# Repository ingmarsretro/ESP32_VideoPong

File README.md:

# ESP32 PAL Pong - Vectorgameboard V1.0

Dieses Projekt ist eine klassische Pong-Umsetzung für den **ESP32**, die ein echtes **PAL-Videosignal** (Composite/FBAS) direkt über einen GPIO erzeugt. Ursprünglich als Demonstration für einen FH-Tag entwickelt, nutzt der Code das volle Potenzial des eigens dafür entwickelten **Vectorgameboards**.

## 🚀 Das Vectorgameboard V1.0
Passend zu dieser Software wurde eine dedizierte Platine entwickelt, die den ESP32 aufnimmt und alle notwendigen Komponenten "on-board" vereint:

*   **All-in-One Design:** Integrierte Potentiometer, Taster sowie Buchsen für Video- und Audio-Out.
*   **Audio-System:** Ein kleiner Lautsprecher samt Verstärker ist direkt auf dem Board verbaut.
*   **Dual-Mode Hardware:** Das Board ist sowohl für Composite-Video (PAL/NTSC) als auch für **ESP Vector Software** (X-Y-Modus für Oszilloskope) ausgelegt.
*   **Externer DAC:** Für die hochpräzise Vektordarstellung ist ein externer DAC verbaut.
*   **Open Hardware:** Details zu den Verbindungen, der Bestückung und dem Design finden sich in den **Schaltplänen** und **Eagle-Layouts** in diesem Repository.

## 📺 Software-Features
*   **PAL-Ausgabe:** Erzeugung eines Composite-Signals auf **PIN 25**.
*   **Spielmodi:** Wahl zwischen Singleplayer (gegen KI) und lokalem Multiplayer (1vs1).
*   **Steuerung:** Analoges Paddle-Feeling durch die Nutzung der On-Board Potentiometer.
*   **Grafik:** Integration von Bitmaps (Avatar/Logo) und Text via Bitluni-Library.
*   **Sound:** Akustisches Feedback bei Ballkontakt, Punktgewinn und Spielende.

## ⚠️ Wichtige Kompilier-Hinweise
Da die Video-Generierung extrem zeitkritisch ist, müssen zwingend folgende Library-Versionen verwendet werden. **Versionen der 3.x.x Schiene sind aktuell nicht kompatibel!**

| Komponente | Version |
| :--- | :--- |
| **ESP32 by Espressif Systems** | `2.0.0` |
| **Arduino ESP32 Boards** | `2.0.11` |
| **bitluni ESP32Lib** | `0.3.1` |

*Hinweis: Beim Kompilieren auftretende Warnungen können ignoriert werden.*

## 🛠 Hardware-Belegung (Pinout)
| Komponente | GPIO | Beschreibung |
| :--- | :--- | :--- |
| **Video Out** | 25 | Composite Signal |
| **Buzzer/Audio** | 27 | Soundausgabe (interner Verstärker) |
| **Poti 1** | 35 | Player 1 (Links) |
| **Poti 2** | 34 | Player 2 (Rechts) |
| **Button 1** | 32 | Modus wechseln |
| **Button 2** | 33 | Start / Aktion |

## 📜 Credits
*   **Hardware & Software:** ingmarsretro (Stand: Feb. 2026)
*   **Video Library:** Ein Dank geht an [bitluni](https://github.com) für die Bereitstellung der `ESP32Lib`.

---
*Viel Spaß beim Retrogaming auf dem Oszilloskop oder Röhrenfernseher!*

# ESP32 PAL Pong - Vectorgameboard V1.0

This project is a classic Pong implementation for the **ESP32**, generating a real **PAL composite video signal** (FBAS) directly via GPIO. originally developed as a demonstration for a university tech-day, this code utilizes the full potential of the custom-designed **Vectorgameboard**.

## 🚀 The Vectorgameboard V1.0
To support this software, a dedicated PCB was developed that houses the ESP32 and integrates all necessary components on-board:

*   **All-in-One Design:** Includes on-board potentiometers, buttons, and dedicated jacks for Video and Audio Out.
*   **Audio System:** Features a built-in small speaker and an integrated amplifier for immediate sound feedback.
*   **Dual-Mode Hardware:** The board is designed for both Composite Video (PAL/NTSC) and **ESP Vector Software** (X-Y mode for oscilloscopes).
*   **External DAC:** A dedicated external DAC is included for high-precision vector rendering on analog screens.
*   **Open Hardware:** Detailed schematics and **Eagle layouts** are available within this repository.

## 📺 Software Features
*   **PAL Output:** Generates a composite signal on **PIN 25**.
*   **Game Modes:** Toggle between Singleplayer (vs. AI) and local Multiplayer (1vs1).
*   **Precision Control:** Authentic analog paddle feeling using the on-board potentiometers.
*   **Graphics:** Integration of custom bitmaps (avatar/logo) and text overlays via the Bitluni library.
*   **Sound:** Haptic audio feedback for ball collisions, scoring, and game-over states.

## ⚠️ Critical Compilation Notes
Video generation on the ESP32 is extremely time-sensitive. To compile successfully, you **must** use the following library versions. **Versions 3.x.x are currently not compatible!**

| Component | Version |
| :--- | :--- |
| **ESP32 by Espressif Systems** | `2.0.0` |
| **Arduino ESP32 Boards** | `2.0.11` |
| **bitluni ESP32Lib** | `0.3.1` |

*Note: You can safely ignore compiler warnings during the build process.*

## 🛠 Hardware Pinout
| Component | GPIO | Description |
| :--- | :--- | :--- |
| **Video Out** | 25 | Composite Signal |
| **Buzzer/Audio** | 27 | Audio Output (Internal Amp) |
| **Pot 1** | 35 | Player 1 (Left) |
| **Pot 2** | 34 | Player 2 (Right) |
| **Button 1** | 32 | Change Mode |
| **Button 2** | 33 | Start / Action |

## 📜 Credits
*   **Hardware & Software:** ingmarsretro (Released: Feb. 2026)
*   **Video Library:** Special thanks to [bitluni](https://github.com) for the excellent `ESP32Lib`.

---
*Have fun retrogaming on your CRT TV or Oscilloscope!*

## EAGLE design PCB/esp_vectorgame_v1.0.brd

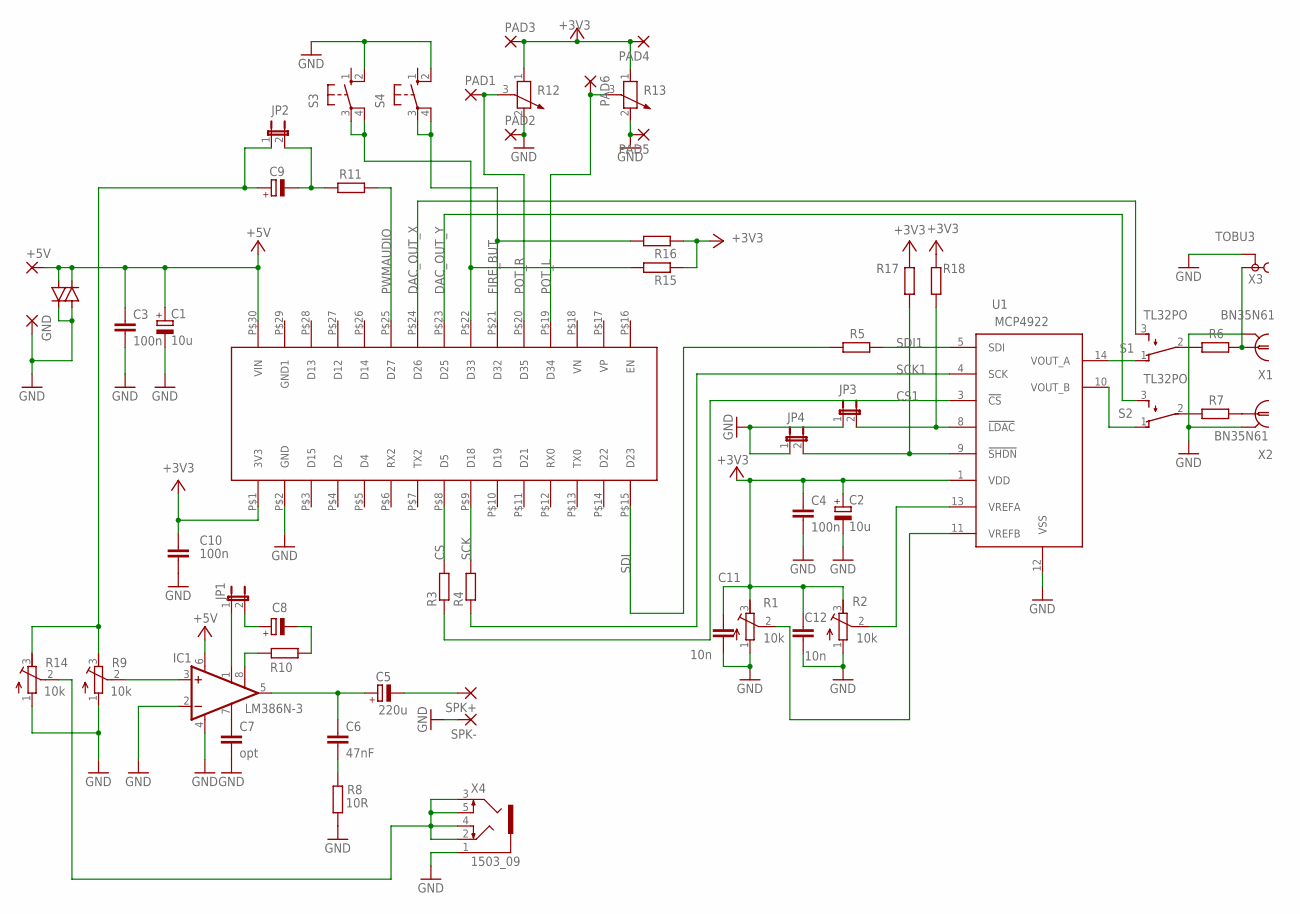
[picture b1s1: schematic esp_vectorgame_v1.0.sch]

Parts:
+5V: 3,81/1,4
C1, C2: 10u; E2,5-6E
C3, C4, C10: 100n; C0805
C5: 220u; E2,5-6E
C6: 47nF; C0805
C7: opt; C0805
C8, C9: CPOL-EUE2,5-6E; E2,5-6E
C11, C12: 10n; C0805
GND: 3,81/1,4
IC1: LM386N-3; DIL08
JP1, JP2, JP3, JP4: JP1E; JP1
PAD1, PAD2, PAD3, PAD4, PAD5, PAD6: 3,81/1,4
R1, R2, R9, R14: 10k; RTRIM64W
R3, R4, R5, R6, R7, R10, R11, R15, R16, R17, R18: R-EU_R0805; R0805
R8: 10R; R0805
R12, R13: POTENTIOMETER_PT-10; PT-10
S1, S2: TL32PO; TL3XPO
S3, S4: 10-XX; B3F-10XX
SPK+: 3,81/1,4
SPK-: 3,81/1,4
TVS1, TVS2: 1N4148DO35-7; DO35-7
U1: MCP4922; SO-14
U$2: ESP_WROOM32; ESP_NODEMCU
X1, X2: BN35N61; B35N61
X3: TOBU3
X4: 1503_09

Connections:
+3V3: C2.+, C4.1, C10.1, C11.1, C12.1, PAD3.1, PAD4.1, R1.3 (E), R2.3 (E), R12.1, R13.1, R15.1, R16.1, R17.1, R18.1, U1.1 (VDD), U$2.P$1 (3V3)
+5V: +5V.1, C1.+, C3.1, IC1.6 (VS), TVS1.C, TVS2.A, U$2.P$30 (VIN)
CS: R3.2, U$2.P$8 (D5)
CS1: R3.1, U1.3 (!CS)
DAC_OUT_X: S1.3 (S), U$2.P$24 (D26)
DAC_OUT_Y: S2.3 (S), U$2.P$23 (D25)
FIRE_BUT: R16.2, S4.3, S4.4 (P1), U$2.P$21 (D32)
GND: C1.-, C2.-, C3.2, C4.2, C7.2, C10.2, C11.2, C12.2, GND.1, IC1.2 (-IN), IC1.4 (GND), JP3.1, JP4.1, PAD2.1, PAD5.1, R1.1 (A), R2.1 (A), R8.1, R9.1 (A), R12.2, R13.2, R14.1 (A), S3.2 (S1), S4.2 (S1), SPK-.1, TVS1.A, TVS2.C, U1.12 (VSS), U$2.P$2 (GND), X1.2, X1.3 (2), X1.4 (2), X1.5 (2), X2.2, X2.3 (2), X2.4 (2), X2.5 (2), X3.2, X3.2@1 (2), X3.2@2 (2), X4.1
unnamed: JP3.2, R18.2, U1.8 (!LDAC)
unnamed: R7.1, X2.1
unnamed: R7.2, S2.2
unnamed: S1.1 (O), U1.14 (VOUT_A)
unnamed: R1.2 (S), U1.11 (VREFB)
unnamed: R2.2 (S), U1.13 (VREFA)
unnamed: S2.1 (O), U1.10 (VOUT_B)
unnamed: R6.1, X1.1, X3.1
unnamed: R6.2, S1.2
unnamed: C6.2, R8.2
unnamed: IC1.1 (GAIN), JP1.1
unnamed: C5.+, C6.1, IC1.5 (OUT)
unnamed: C7.1, IC1.7 (BYPASS)
unnamed: IC1.3 (+IN), R9.2 (S)
unnamed: C8.+, JP1.2
unnamed: IC1.8 (GAIN), R10.2
unnamed: C8.-, R10.1
unnamed: C9.-, JP2.2, R11.2
unnamed: C9.+, JP2.1, R9.3 (E), R14.3 (E)
unnamed: R14.2 (S), X4.2, X4.3, X4.4, X4.5
unnamed: C5.-, SPK+.1
unnamed: R15.2, S3.3, S3.4 (P1), U$2.P$22 (D33)
unnamed: JP4.2, R17.2, U1.9 (!SHDN)
POT_L: PAD6.1, R13.3, U$2.P$19 (D34)
POT_R: PAD1.1, R12.3, U$2.P$20 (D35)
PWMAUDIO: R11.1, U$2.P$25 (D27)
SCK: R4.2, U$2.P$9 (D18)
SCK1: R4.1, U1.4 (SCK)
SDI: R5.2, U$2.P$15 (D23)
SDI1: R5.1, U1.5 (SDI)

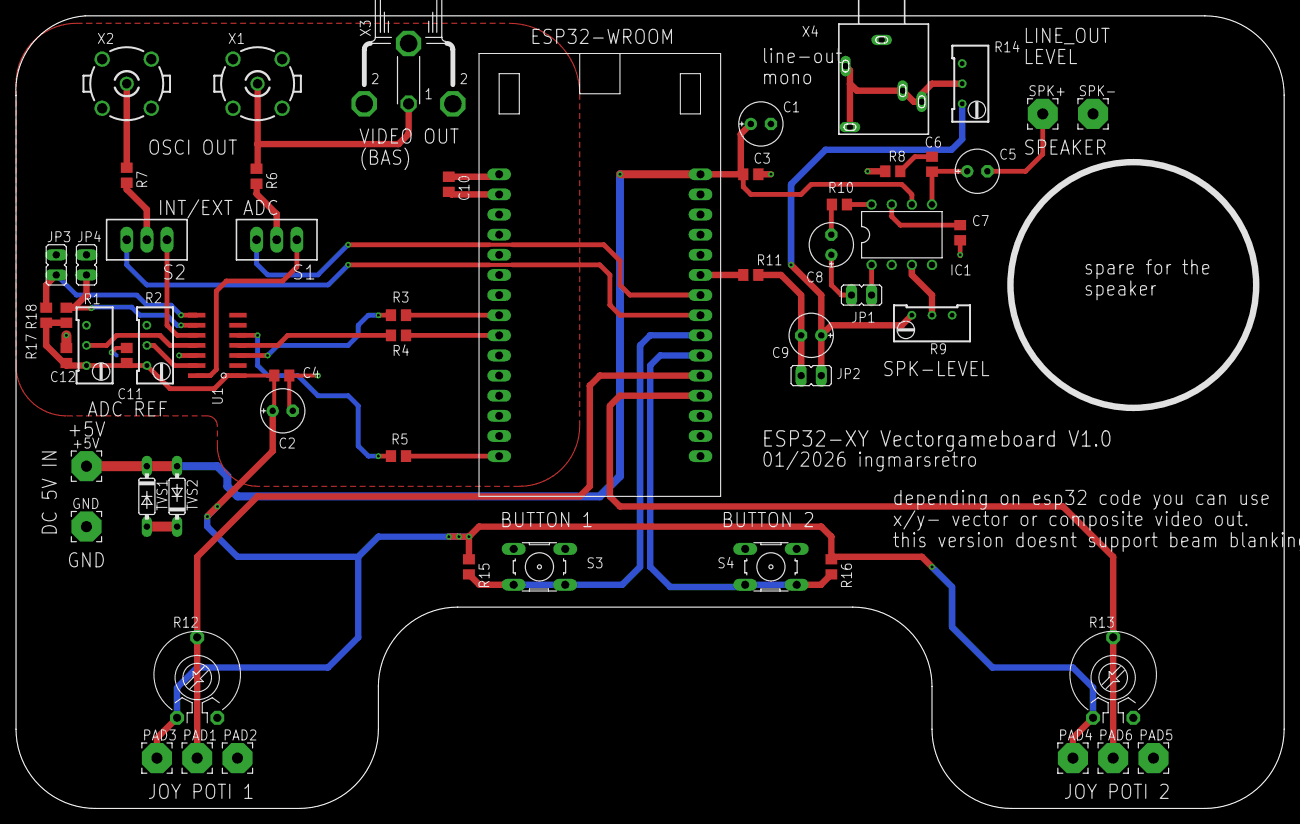
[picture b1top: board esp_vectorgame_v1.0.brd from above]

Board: 2 copper layers, 160.0 x 100.0 mm, 57 parts (0 on the bottom side), 38 nets.

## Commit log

2026-02-13 Add files via upload
    V1.0
